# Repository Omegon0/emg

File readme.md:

# EMGauntlet

Based on project at https://hackaday.io/project/8823-super-simple-muscle-emg-sensor/details

Muscles create many action potentials during a movement, like moving your arm or closing your hands. This creates a measurable signal, which shows an increase in signal due to different fingers moving. (Hackaday)

This project extends the Hackaday project to wirelessly communicate the EMG signals to another device.

Why did I make this? Because it's cool. Also, current medical EMG procedures are more invasive and they hurt so this is a better (albeit less precise) alternative. 

### BOM

|Ref                   |Qnty|Value                      |Cmp name                   |Footprint                                                     |Description                                                                                                           |Vendor |Link                                                                                                                                                |
|----------------------|----|---------------------------|---------------------------|--------------------------------------------------------------|----------------------------------------------------------------------------------------------------------------------|-------|----------------------------------------------------------------------------------------------------------------------------------------------------|
|C1                    |1   |47uF                       |C                          |Capacitor_SMD:C_0805_2012Metric                               |Unpolarized capacitor                                                                                                 |Digikey|https://www.digikey.com/en/products/detail/samsung-electro-mechanics/CL21A476MQYNNNG/3894447                                                        |
|C2, C3, C4, C5, C6, C7|3   |10uF                       |C                          |Capacitor_SMD:C_0805_2012Metric                               |Unpolarized capacitor                                                                                                 |Digikey|https://www.digikey.com/en/products/detail/taiyo-yuden/LMK212BJ106KG-T/930652                                                                       |
|C8, C9                |2   |1uF                        |C                          |Capacitor_SMD:C_0805_2012Metric                               |Unpolarized capacitor                                                                                                 |Digikey|https://www.digikey.com/en/products/detail/samsung-electro-mechanics/CL21B105KBFNNNE/3886687                                                        |
|D1                    |1   |D                          |D                          |Diode_SMD:D_0805_2012Metric                                   |Diode                                                                                                                 |Digikey|https://www.digikey.com/en/products/detail/kyocera-avx/SD0805S020S0R5/3749524                                                                       |
|D2                    |1   |LED                        |LED                        |LED_SMD:LED_0805_2012Metric                                   |Light emitting diode                                                                                                  |Digikey|https://www.digikey.com/en/products/detail/ams-osram-usa-inc/LG-R971-KN-1-0-20-R18/1227925                                                          |
|D3                    |1   |D_Schottky                 |D_Schottky                 |Diode_SMD:D_SMA                                               |Schottky diode                                                                                                        |Digikey|https://www.digikey.com/en/products/detail/mcc-micro-commercial-components/SK54A-LTP/5114132?s=N4IgTCBcDaIMoGkCsAWAggWgDIBUAKIAugL5A                |
|J1                    |1   |Conn_01x02_Pin             |Conn_01x02_Pin             |Connector_JST:JST_PH_S2B-PH-SM4-TB_1x02-1MP_P2.00mm_Horizontal|Generic connector, single row, 01x02, script generated                                                                |Digikey|https://www.digikey.com/en/products/detail/jst-sales-america-inc/S2B-PH-SM4-TB/926655?s=N4IgTCBcDaIMpgEIFoAKAJZcCyAWZAKogBQAyAYgJTFwBylIAugL5A      |
|J3                    |1   |USB_C_Receptacle_USB2.0_16P|USB_C_Receptacle_USB2.0_16P|Connector_USB:AMPHENOL_12402012E212A                          |USB 2.0-only 16P Type-C Receptacle connector                                                                          |Digikey|https://www.digikey.com/en/products/detail/amphenol-cs-commercial-products/12402012E212A/13683192                                                   |
|R1                    |1   |5.7k                       |R                          |Resistor_SMD:R_0805_2012Metric                                |Resistor                                                                                                              |Amazon |https://www.amazon.com/Yobett-ohm-8850pcs-Resistor-Sample/dp/B013B55KQE?source=ps-sl-shoppingads-lpcontext&ref_=fplfs&smid=A3SC7BPT5ZUZY6&gQT=1&th=1|
|R2                    |1   |1k                         |R                          |Resistor_SMD:R_0805_2012Metric                                |Resistor                                                                                                              |Amazon |https://www.amazon.com/Yobett-ohm-8850pcs-Resistor-Sample/dp/B013B55KQE?source=ps-sl-shoppingads-lpcontext&ref_=fplfs&smid=A3SC7BPT5ZUZY6&gQT=1&th=1|
|R3, R4                |2   |100k                       |R                          |Resistor_SMD:R_0805_2012Metric                                |Resistor                                                                                                              |Amazon |https://www.amazon.com/Yobett-ohm-8850pcs-Resistor-Sample/dp/B013B55KQE?source=ps-sl-shoppingads-lpcontext&ref_=fplfs&smid=A3SC7BPT5ZUZY6&gQT=1&th=1|
|R6, R7, R8            |3   |5.1k                       |R                          |Resistor_SMD:R_0805_2012Metric                                |Resistor                                                                                                              |Amazon |https://www.amazon.com/Yobett-ohm-8850pcs-Resistor-Sample/dp/B013B55KQE?source=ps-sl-shoppingads-lpcontext&ref_=fplfs&smid=A3SC7BPT5ZUZY6&gQT=1&th=1|
|SW1                   |1   |SW_SPST                    |SW_SPST                    |Button_Switch_SMD:SW_DPDT_CK_JS202011JCQN                     |Single Pole Single Throw (SPST) switch                                                                                |Digikey|https://www.digikey.com/en/products/detail/c-k/JS202011JCQN/6137630?s=N4IgTCBcDaIFIGUwAYUEY1wMIEUByIAugL5A                                          |
|SW3, SW4              |2   |SW_Push                    |SW_Push                    |Button_Switch_SMD:SW_TS04-66-50-BK-160-SMT                    |Push button switch, generic, two pins                                                                                 |Digikey|https://www.digikey.com/en/products/detail/cts-electrocomponents/222AMVBAR/5227982                                                                  |
|U1                    |1   |INA128                     |INA128UA                   |Package_SO:SOIC-8-1EP_3.9x4.9mm_P1.27mm_EP2.29x3mm            |Precision, Low Power Instrumentation Amplifier G = 1 + 50kOhm/Rg, DIP-8/SOIC-8                                        |Digikey|https://www.digikey.com/en/products/detail/texas-instruments/INA128UA/300997                                                                        |
|U3                    |1   |MCP73831T-2ACI_OT          |MCP73831T-2ACI_OT          |open-Smartwatch:SOT-23-5                                      |IC CONTROLLR LI-ION 4.2V SOT23-5                                                                                      |Digikey|https://www.digikey.com/en/products/detail/microchip-technology/MCP73831T-2ACI-OT/964301                                                            |
|U4                    |1   |DMG3415U-7                 |DMG3415U-7                 |Package_TO_SOT_SMD:SOT95P240X105-3N                           |                                                                                                                      |Digikey|https://www.digikey.com/en/products/detail/diodes-incorporated/dmg3415u-7/2052768                                                                   |
|U5                    |1   |AP2112K-3.3                |AP2112K-3.3                |Package_TO_SOT_SMD:SOT-23-5                                   |600mA low dropout linear regulator, with enable pin, 3.8V-6V input voltage range, 3.3V fixed positive output, SOT-23-5|Digikey|https://www.digikey.com/en/products/detail/diodes-incorporated/AP2112K-3-3TRG1/4470746?s=N4IgTCBcDaIIIAUwEZlgNIFoDMA6bIAugL5A                       |
|U6                    |1   |ESP32-S3-WROOM-1-N16R2     |ESP32-S3-WROOM-1-N16R2     |RF_Module:ESP32-S3-WROOM-1                                    |                                                                                                                      |Digikey|https://www.digikey.com/en/products/detail/espressif-systems/esp32-s3-wroom-1-n16r8/16162642                                                        |

# Schematic and PCB

Use example circuits. Otherwise you might end up learning too much electrical engineering and that's not good! 
Hardest part was figuring out the footprints because most of the components I used were not in Kicad and its just annoying
PCB was wired up using FreeRouting

# Firmware

Just used the analog read program built into Arduino IDE to collect data

# CAD

This depends HEAVILY on the person and its strongly recommended to use photogrammetry to figure it out properly. Also the electrode placement will vary from person to person.

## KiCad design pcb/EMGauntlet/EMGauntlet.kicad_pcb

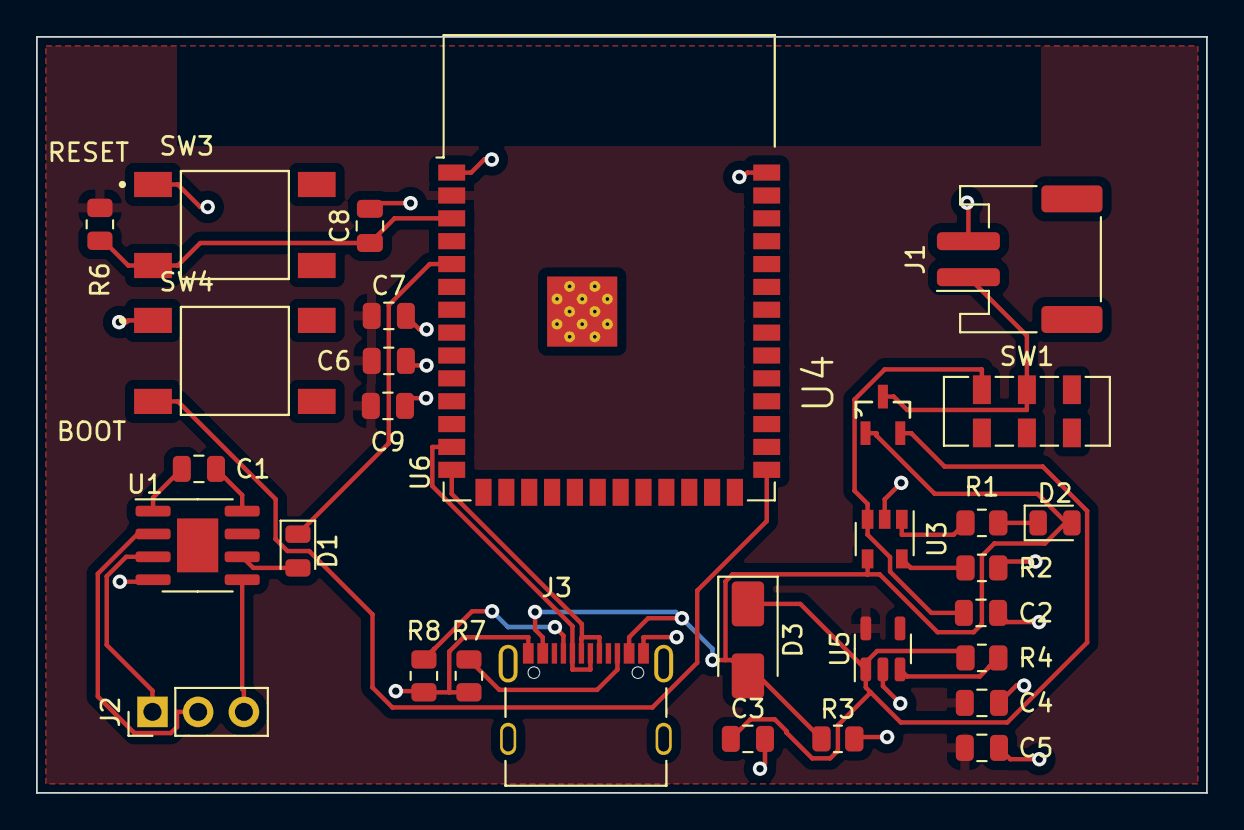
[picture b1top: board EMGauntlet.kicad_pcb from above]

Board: 2 copper layers, 65.0 x 42.0 mm, 30 parts (0 on the bottom side), 23 nets.

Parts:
C1: C; C_0805_2012Metric
C2, C6, C7: 10uF; C_0805_2012Metric
C3, C4, C5: 10uF C; C_0805_2012Metric
C8, C9: 1uF; C_0805_2012Metric
D1: D; D_0805_2012Metric
D2: LED; LED_0805_2012Metric
D3: D_Schottky; D_SMA
J1: Conn_01x02_Pin; JST_PH_S2B-PH-SM4-TB_1x02-1MP_P2.00mm_Horizontal
J2: Conn_01x03_Pin; PinHeader_1x03_P2.54mm_Vertical
J3: USB_C_Receptacle_USB2.0_16P; AMPHENOL_12402012E212A
R1: 5.7k; R_0805_2012Metric
R2: 1k; R_0805_2012Metric
R3, R4: 100k; R_0805_2012Metric
R6, R7, R8: 5.1k; R_0805_2012Metric
SW1: SW_SPST; SW_DPDT_CK_JS202011JCQN
SW3, SW4: SW_Push; SW_TS04-66-50-BK-160-SMT
U1: INA128; SOIC-8-1EP_3.9x4.9mm_P1.27mm_EP2.29x3mm
U3: MCP73831T-2ACI_OT; SOT-23-5
U4: DMG3415U-7; SOT95P240X105-3N
U5: AP2112K-3.3; SOT-23-5
U6: ESP32-S3-WROOM-1-N16R2; ESP32-S3-WROOM-1

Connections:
+3V3: C4.1, C5.1, C6.1, C7.1, C9.1, R6.1, U1.7 (V+), U5.5 (VOUT), U6.2 (3V3)
/BOOT: SW4.2, U6.27 (IO0)
/D+: J3.A6 (D+), J3.B6 (D+), U6.14 (IO20)
/D-: J3.A7 (D-), J3.B7 (D-), U6.13 (IO19)
/IN1: J2.1, U1.3 (+)
/IN2: J2.2, U1.2 (-)
/OUT: D1.1 (K), U6.5 (IO5)
/REF: J2.3, U1.5 (Ref)
/RESET: C8.1, R6.2, SW3.2, U6.3 (EN)
GND: C2.2, C3.2, C4.2, C5.2, C6.2, C7.2, C8.2, C9.2, J1.2, J3.A1 (GND), J3.B1 (GND), R2.2, R3.2, R7.2, R8.2, SW3.1, SW4.1, U1.4 (V-), U3.2 (VSS), U5.2 (GND), U6.1 (GND), U6.40 (GND)
unnamed: C1.1, U1.1 (Rg)
unnamed: C1.2, U1.8 (Rg)
unnamed: D1.2 (A), U1.6
unnamed: D2.1 (K), R1.1
unnamed: C3.1, D3.1 (K), R4.1, U4.2 (S), U5.1 (VIN)
unnamed: J3.A5 (CC1), R8.1
unnamed: J3.B5 (CC2), R7.1
unnamed: C2.1, SW1.1 (A), U3.3 (VBAT)
unnamed: R2.1, U3.5 (PROG)
unnamed: R1.2, U3.1 (STAT)
unnamed: R4.2, U5.3 (EN)
VBAT: J1.1, SW1.2 (B), U4.3 (D)
VBUS: D2.2 (A), D3.2 (A), J3.A4 (VBUS), J3.B4 (VBUS), R3.1, U3.4 (VDD), U4.1 (G)

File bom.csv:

Ref,Qnty,Value,Cmp name,Footprint,Description,Vendor,Link,Price,Total price
C1,1,47uF,C,Capacitor_SMD:C_0805_2012Metric,Unpolarized capacitor,Digikey,https://www.digikey.com/en/products/detail/samsung-electro-m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,0.27,0.27
"C2, C3, C4, C5, C6, C7",3,10uF,C,Capacitor_SMD:C_0805_2012Metric,Unpolarized capacitor,Digikey,https://www.digikey.com/en/products/detail/taiyo-yuden/LMK21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,$0.08 ,0.24
"C8, C9",2,1uF,C,Capacitor_SMD:C_0805_2012Metric,Unpolarized capacitor,Digikey,https://www.digikey.com/en/products/detail/samsung-electro-m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,0.08,0.16
D1,1,D,D,Diode_SMD:D_0805_2012Metric,Diode,Digikey,https://www.digikey.com/en/products/detail/kyocera-avx/SD080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,0.34,0.34
D2,1,LED,LED,LED_SMD:LED_0805_2012Metric,Light emitting diode,Digikey,https://www.digikey.com/en/products/detail/ams-osram-usa-inc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,0.15,0.15
D3,1,D_Schottky,D_Schottky,Diode_SMD:D_SMA,Schottky diode,Digikey,https://www.digikey.com/en/products/detail/mcc-micro-commerc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,0.33,0.33
J1,1,Conn_01x02_Pin,Conn_01x02_Pin,Connector_JST:JST_PH_S2B-PH-SM4-TB_1x02-1MP_P2.00mm_Horizontal,"Generic connector, single row, 01x02, script generated",Digikey,https://www.digikey.com/en/products/detail/jst-sales-america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,0.48,0.48
J3,1,USB_C_Receptacle_USB2.0_16P,USB_C_Receptacle_USB2.0_16P,Connector_USB:AMPHENOL_12402012E212A,USB 2.0-only 16P Type-C Receptacle connector,Digikey,https://www.digikey.com/en/products/detail/amphenol-cs-comme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,0.58,0.58
R1,1,5.7k,R,Resistor_SMD:R_0805_2012Metric,Resistor,Amazon,https://www.amazon.com/Yobett-ohm-8850pcs-Resistor-Sample/dp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,25.99,25.99
R2,1,1k,R,Resistor_SMD:R_0805_2012Metric,Resistor,Amazon,https://www.amazon.com/Yobett-ohm-8850pcs-Resistor-Sample/dp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,0,0
"R3, R4",2,100k,R,Resistor_SMD:R_0805_2012Metric,Resistor,Amazon,https://www.amazon.com/Yobett-ohm-8850pcs-Resistor-Sample/dp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,0,0
"R6, R7, R8",3,5.1k,R,Resistor_SMD:R_0805_2012Metric,Resistor,Amazon,https://www.amazon.com/Yobett-ohm-8850pcs-Resistor-Sample/dp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,0,0
SW1,1,SW_SPST,SW_SPST,Button_Switch_SMD:SW_DPDT_CK_JS202011JCQN,Single Pole Single Throw (SPST) switch,Digikey,https://www.digikey.com/en/products/detail/c-k/JS202011JCQN/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,0.84,0.84
"SW3, SW4",2,SW_Push,SW_Push,Button_Switch_SMD:SW_TS04-66-50-BK-160-SMT,"Push button switch, generic, two pins",Digikey,https://www.digikey.com/en/products/detail/cts-electrocompon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,0.22,0.44
U1,1,INA128,INA128UA,Package_SO:SOIC-8-1EP_3.9x4.9mm_P1.27mm_EP2.29x3mm,"Precision, Low Power Instrumentation Amplifier G = 1 + 50kOhm/Rg, DIP-8/SOIC-8",Digikey,https://www.digikey.com/en/products/detail/texas-instruments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,10.09,10.09
U3,1,MCP73831T-2ACI_OT,MCP73831T-2ACI_OT,open-Smartwatch:SOT-23-5,IC CONTROLLR LI-ION 4.2V SOT23-5,Digikey,https://www.digikey.com/en/products/detail/microchip-technol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,0.76,0.76
U4,1,DMG3415U-7,DMG3415U-7,Package_TO_SOT_SMD:SOT95P240X105-3N,,Digikey,https://www.digikey.com/en/products/detail/diodes-incorporat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,0.45,0.45
U5,1,AP2112K-3.3,AP2112K-3.3,Package_TO_SOT_SMD:SOT-23-5,"600mA low dropout linear regulator, with enable pin, 3.8V-6V input voltage range, 3.3V fixed positive output, SOT-23-5",Digikey,https://www.digikey.com/en/products/detail/diodes-incorporat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,0.22,0.22
U6,1,ESP32-S3-WROOM-1-N16R2,ESP32-S3-WROOM-1-N16R2,RF_Module:ESP32-S3-WROOM-1,,Digikey,https://www.digikey.com/en/products/detail/espressif-systems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,6.56,6.56
,,,,,,,,,47.9
,,,,,,,,,
PCB options and cost,1,JLCPCB,$3.10 ,Shipping: $3?,,,,,
,,,,,,,,,
Final total,$54.00 ,,,,,,,,
,,,,,,,,,
Cost with JLC PCBA:,,$87.10 ,,,,,,,
,,Cost with shipping and tariffs,150,,,,,,

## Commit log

2025-07-15 Added journal and readme
2025-07-15 updated journal
2025-07-15 added images
2025-07-16 added pcb files
2025-07-16 added bom and journal updates
2025-07-16 updated bom and journal
2025-07-17 updated journal and readme, added renders, full BOM
2025-07-19 fixed bom
2025-07-23 pcba bom
2025-08-24 file dump
